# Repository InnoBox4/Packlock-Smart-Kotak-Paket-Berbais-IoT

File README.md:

# Packlock
## Smart-Kotak-Paket-Berbasis-IoT

Proyek ini bertujuan untuk mengembangkan smart kotak paket berbasis IoT bernama PackLock, yang memungkinkan pengguna memantau status keberadaan paket secara real-time melalui dashboard web berbasis PHP. Sistem ini dirancang sebagai solusi pengiriman barang tanpa tatap muka yang aman dan efisien, terutama di era digital saat ini. PackLock dibangun menggunakan Arduino Uno sebagai mikrokontroler utama yang mengatur pembacaan sensor, kontrol aktuator, dan komunikasi data ke server lokal.

Untuk mendeteksi keberadaan paket, sistem menggunakan sensor infrared yang dipasang di dalam kotak. Selain itu, sensor ultrasonik dan reed switch digunakan untuk memantau status pintu depan dan pintu belakang kotak, apakah dalam keadaan tertutup atau terbuka. Ketika kondisi berubah, sistem akan mengirimkan data ke server melalui komunikasi serial dan hasilnya ditampilkan pada web secara real-time. Pengguna juga dapat menerima notifikasi dan melakukan kontrol jarak jauh melalui dashboard, termasuk membuka pintu kotak secara otomatis.

Web dashboard PackLock dibangun menggunakan PHP yang terhubung ke database untuk menyimpan dan menampilkan status terkini dari kotak paket. Dengan antarmuka yang sederhana, pengguna dapat dengan mudah mengetahui apakah terdapat paket di dalam kotak dan apakah pintu dalam keadaan tertutup atau terbuka. Sistem ini diharapkan dapat meningkatkan keamanan dan efisiensi dalam proses pengiriman dan pengambilan paket di lingkungan rumah atau perkantoran cerdas (smart building).

## Support By :
>- Dosen Pengampu : Akhmad Hendriawan ST., MT. (NIP.197501272002121003)
>- Mata kuliah : Workshop Mikrokontroller
>- Program Studi : D3 Teknik Elektronika
>- Politeknik Elektronika Negeri Surabaya<br>

## Team Member :
|      NRP      |            Nama             |         Jobdesk          |
| :-----------: | :-------------------------: | :----------------------: |
| 2123500023    | Muhammad Fariz Ibnu T.H     | Hardware Developer       | 
| 2123500011    | M . Ghozali                 | Mekanik                  | 
| 2123500013    | Gede Satya Prawira Negara   | Programer               | 
| 2123500008    | M . Ragita Dwi Yuliansyah   | Project Manager (PM)                  | 
| 2123500012    | Setyo Budi Utomo            | Mekanik                  | 
| 2123500021    | Adam Surya Waskito          | UI/UX Designer           |

## Komponen Utama 
| Komponen |             Fungsi                | 
|----------|-----------------------------------|                       
|Arduino Uno| pengontrol sistem |
| Ultrasonic Sensor HC-SR04  | deteksi pintu depan tertutup atau tidak |               
|Sensor Infrared (IR) Proximity FC-51 |deteksi paket masuk|
|Reed Switch + Magnet | deteksi pintu belakang terbuka/tertutup)|
|Servo Motor (SG90 / MG90S)|untuk membuka pintu|

## Flyer Packlock

## Cara kerja Packlock

https://github.com/user-attachments/assets/c9181a2b-23b7-4780-8032-19ebb1beb945

## Iklan Produk Packlock

[Video Iklan Produk Packlock](https://youtube.com/shorts/VkG0_1tyrqw?feature=share)

## PPT Packlock

[PPT Packlock](https://www.canva.com/design/DAGpCFjL8s4/J2JU336eNsQ9mIj8pktKxA/edit?utm_content=DAGpCFjL8s4&utm_campaign=designshare&utm_medium=link2&utm_source=sharebutton)

## Desain App di Figma

[Desain App Packlock di Figma](https://www.figma.com/design/fq3XM4EmNfqJVly56ajVYE/Packlock?node-id=0-1&t=N5Q5iODnZTlXCq0t-1)

## Desain 3D di Thingiverse 

[Desain 3D di Thingiverse](https://www.thingiverse.com/setyoo_io/collections/43256436/things)

## Simulasi Program di Wokwi

[Simulasi Program di Wokwi](https://wokwi.com/projects/429229658305672193)

## Video Simulasi Program

[Video Simulasi Program](https://github.com/user-attachments/assets/82a5f85e-70d9-47c1-b36e-2be93320dba2)

## Daftar Isi
- [Komponen Yang Digunakan](#Komponen-Yang-Digunakan)
- [Blok Diagram](#Blok-Diagram)
- [Diagram Arsitektur Sistem](#Diagram-Arsitektur-Sistem)
- [Hardware](#Hardware)
- [Desain UI UX](#Desain-UI-UX)
- [Desain 3D](#Desain-3D)
- [Desain Yang Sudah Jadi](#Desain-Yang-Sudah-Jadi)

## Komponen Yang Digunakan
1.Hardware
- Arduino Uno
- Motor Servo
- Sensor IR Obstacle
- Sensor Ultrasonik
- Conector Molex
- Shield PCB
- Kabel Jumper

2.Software
- Arduino IDE
- Visual Studio Code
- Kicad
- Inventor
- Figma
- Wokwi

3.Alat 
- Palu
- Meteran
- Gergaji
- Penggaris
- bulpoint
- Cutter
- Gunting
- Kuas
- Obeng
- Lem Tembak
- Solder 
  
4.Bahan
- Balok kayu Diameter 2 CM (5 Buah)
- Karton
- Paku Kecil
- Lem kayu
- Cat Kayu
- Paku Pines
- Cat putih
- Timah
- Solasi

## Desain Yang Sudah Jadi

## Blok Diagram

## Diagram Arsitektur Sistem

## [Hardware](https://github.com/InnoBox4/Packlock-Smart-Kotak-Paket-Berbais-IoT/tree/main/HARDWARE)

Berikut ini adalah hasil skematik dari rangkaian Smart Kotak Paket Berbasis IoT menggunakan software KiCad.
<div align="center">

</div>

Berikut ini adalah hasil layout dari rangkaian Smart Kotak Paket Berbasis IoT menggunakan software KiCad.
<div align="center">

</div>

Berikut ini adalah hasil 3D dari rangkaian Smart Kotak Paket Berbasis IoT menggunakan software KiCad.
<div align="center">

</div>

Berikut ini adalah hasil cetak dari rangkaian Smart Kotak Paket Berbasis IoT menggunakan software KiCad.
<div align="center">

</div>

Berikut ini adalah hardware yang sudah terpasang di Packlock.
<div align="center">

</div>

## [Desain UI UX](https://github.com/InnoBox4/Packlock-Smart-Kotak-Paket-Berbais-IoT/tree/main/UI-UX)

Berikut ini adalah UI/UX Web Packlock.
<div align="center">

</div>

## [Desain 3D](https://github.com/InnoBox4/Packlock-Smart-Kotak-Paket-Berbais-IoT/tree/main/DESAIN%203D)

Berikut ini adalah Desain 3D Packlock Bagian Dalam.
<div align="center">

</div>

Berikut ini adalah Desain 3D Packlock Tampak Depan.
<div align="center">

</div>

Berikut ini adalah pembuatan Desain 3D Packlock.

https://github.com/user-attachments/assets/38ecc393-ebad-4563-a7b1-a252cfec6f6e

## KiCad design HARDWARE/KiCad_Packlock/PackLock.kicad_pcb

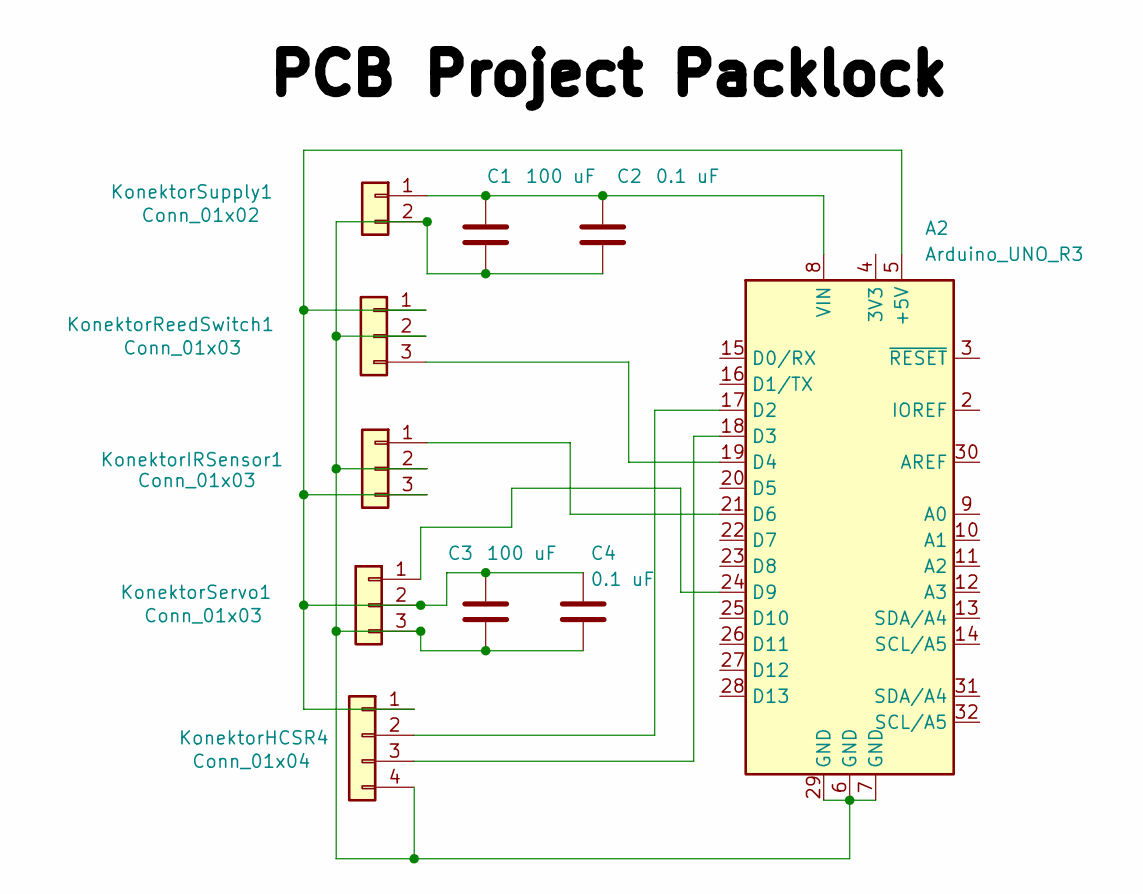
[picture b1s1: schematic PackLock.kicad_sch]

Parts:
A2: Arduino_UNO_R3
C1, C3: 100 uF; C_0805_2012Metric_Pad1.18x1.45mm_HandSolder
C2, C4: 0.1 uF; C_0805_2012Metric_Pad1.18x1.45mm_HandSolder
KonektorHCSR4: Conn_01x04; JST_PH_B4B-PH-K_1x04_P2.00mm_Vertical
KonektorIRSensor1: Conn_01x03; JST_PH_B3B-PH-K_1x03_P2.00mm_Vertical
KonektorReedSwitch1: Conn_01x03; JST_PH_B3B-PH-K_1x03_P2.00mm_Vertical
KonektorServo1: Conn_01x03; JST_PH_B3B-PH-K_1x03_P2.00mm_Vertical
KonektorSupply1: Conn_01x02; JST_PH_B2B-PH-K_1x02_P2.00mm_Vertical

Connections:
unnamed: A2.5 (+5V), C3.1, C4.1, KonektorHCSR4.1, KonektorIRSensor1.3, KonektorReedSwitch1.1, KonektorServo1.2
unnamed: A2.17 (D2), KonektorHCSR4.2
unnamed: A2.18 (D3), KonektorHCSR4.3
unnamed: A2.19 (D4), KonektorReedSwitch1.3
unnamed: A2.21 (D6), KonektorIRSensor1.1
unnamed: A2.24 (D9), KonektorServo1.1
unnamed: A2.8 (VIN), C1.1, C2.1, KonektorSupply1.1
unnamed: A2.6 (GND), A2.7 (GND), A2.29 (GND), C1.2, C2.2, C3.2, C4.2, KonektorHCSR4.4, KonektorIRSensor1.2, KonektorReedSwitch1.2, KonektorServo1.3, KonektorSupply1.2

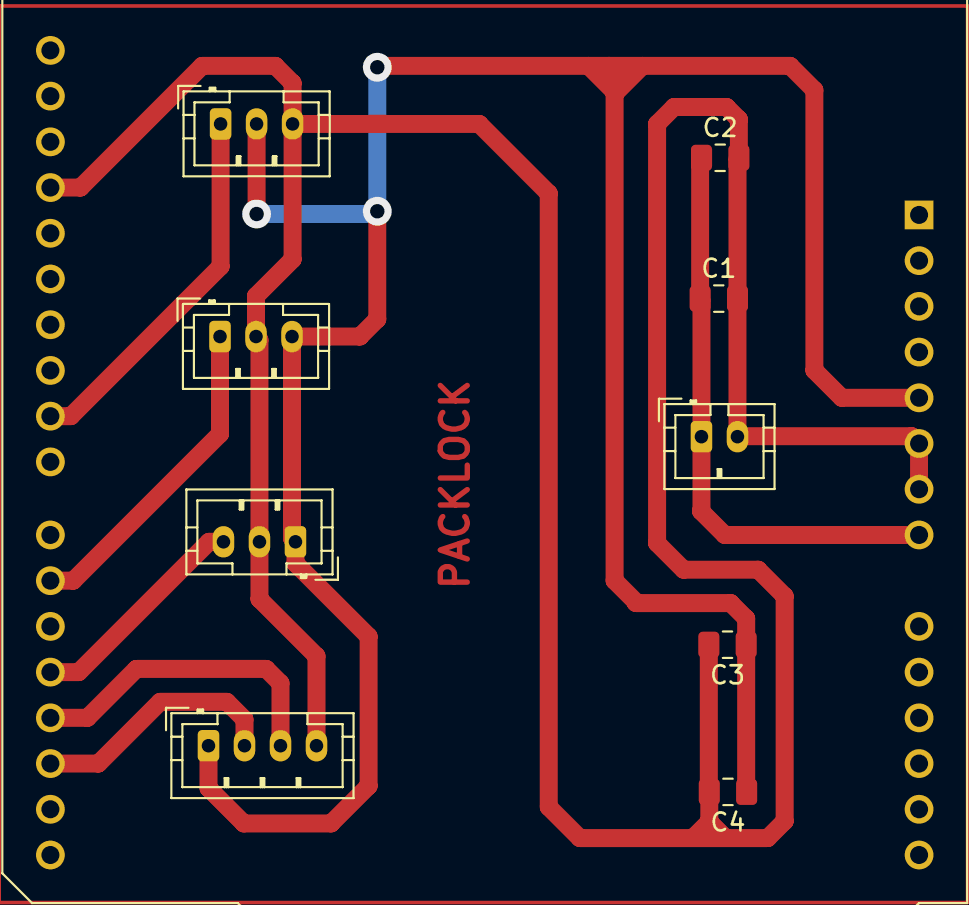
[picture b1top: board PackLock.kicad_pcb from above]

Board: 2 copper layers, 10 parts (0 on the bottom side), 8 nets.

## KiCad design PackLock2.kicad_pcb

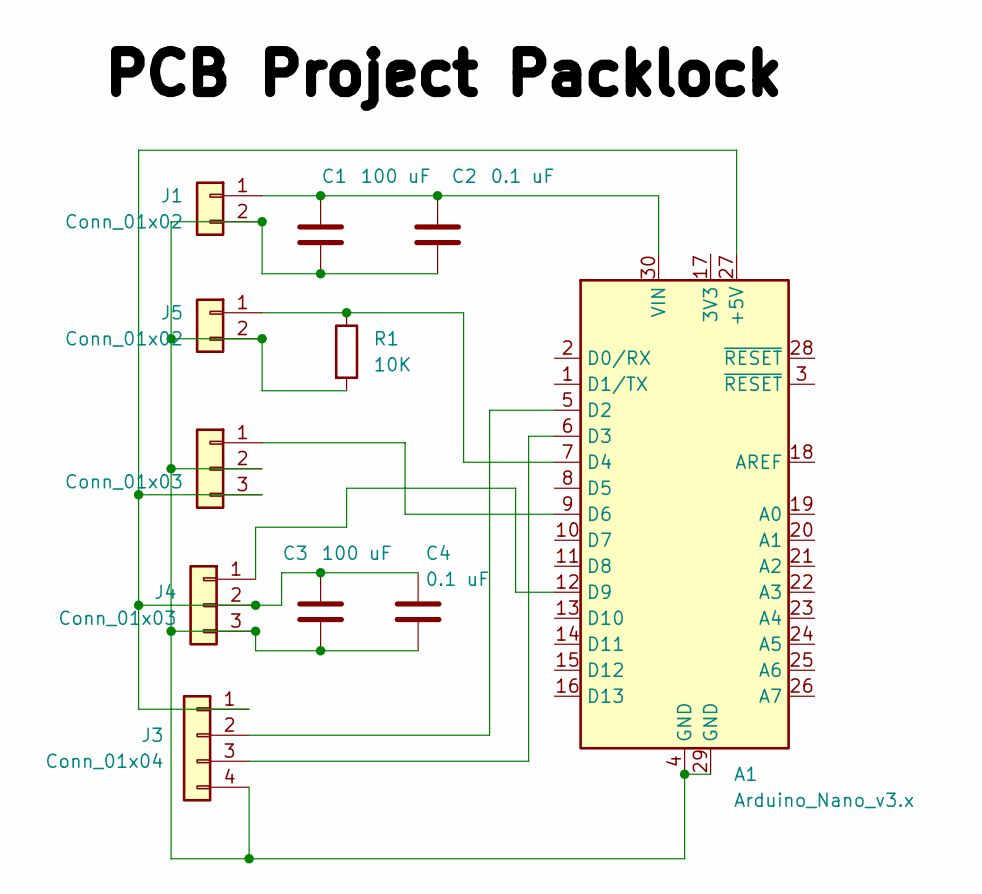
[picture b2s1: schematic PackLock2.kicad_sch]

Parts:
A1: Arduino_Nano_v3.x; Arduino_Nano
C1, C3: 100 uF; CP_Radial_D5.0mm_P2.00mm
C2, C4: 0.1 uF; C_Disc_D3.0mm_W1.6mm_P2.50mm
J1, J5: Conn_01x02; JST_XH_B2B-XH-A_1x02_P2.50mm_Vertical
J2, J4: Conn_01x03; JST_XH_B3B-XH-A_1x03_P2.50mm_Vertical
J3: Conn_01x04; JST_XH_B4B-XH-A_1x04_P2.50mm_Vertical
R1: 10K; R_Axial_DIN0207_L6.3mm_D2.5mm_P7.62mm_Horizontal

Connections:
unnamed 0: A1.27 (+5V), C3.1, C4.1, J2.3, J3.1, J4.2; also elsewhere on the board
unnamed: A1.5 (D2), J3.2
unnamed: A1.6 (D3), J3.3
unnamed: A1.7 (D4), J5.1, R1.1
unnamed 4: A1.9 (D6), J2.1; also elsewhere on the board
unnamed: A1.12 (D9), J4.1
unnamed: A1.30 (VIN), C1.1, C2.1, J1.1
unnamed 7: A1.4 (GND), A1.29 (GND), C1.2, C2.2, C3.2, C4.2, J1.2, J2.2, J3.4, J4.3, J5.2, R1.2; also elsewhere on the board

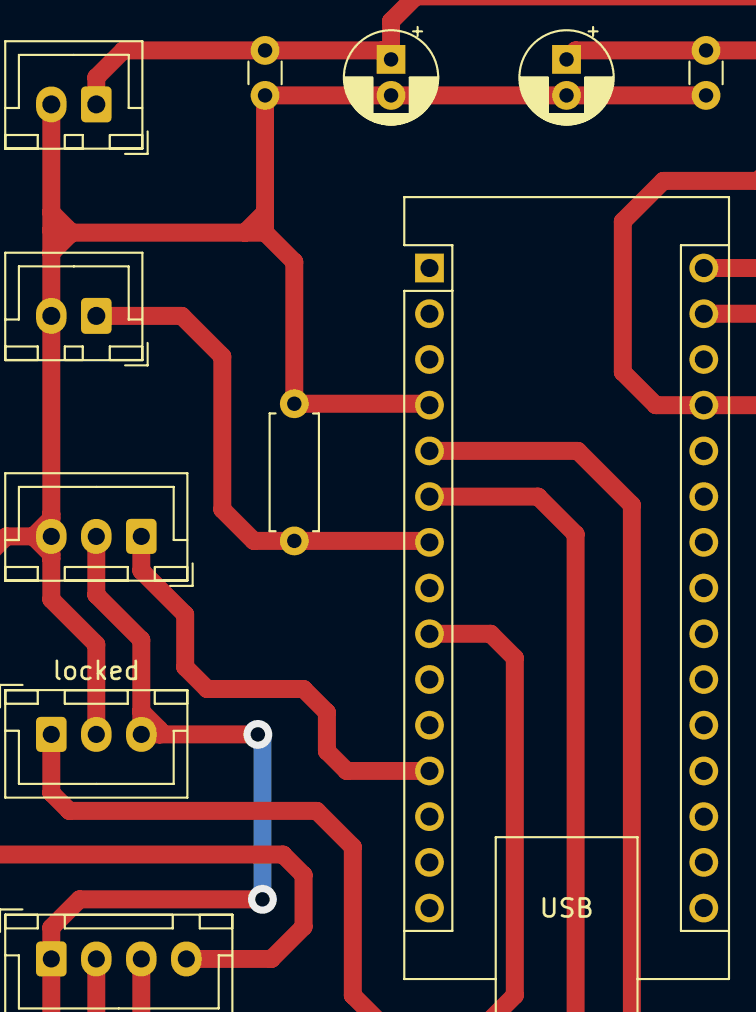
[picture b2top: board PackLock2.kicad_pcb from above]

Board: 2 copper layers, 11 parts (0 on the bottom side), 8 nets.

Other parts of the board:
locked: Conn_01x03; JST_XH_B3B-XH-A_1x03_P2.50mm_Vertical

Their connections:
unnamed 0: locked.3; also elsewhere on the board
unnamed 4: locked.1; also elsewhere on the board
unnamed 7: locked.2; also elsewhere on the board

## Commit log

2025-04-26 Create Desain
2025-04-27 Create Hardware
2025-04-27 Create PCB_Desain
2025-04-27 Rename PCB_Desain to PCB_Desain.png
2025-04-27 Rename PCB_Desain.png to ...
2025-04-27 Rename 3D_PCB_Desain.jpg to Hardware2/3D_PCB_Desain.jpg
2025-04-27 Rename 3D_PCB_Desain.jpg to 3D_PCB_Desain.jpg
2025-04-27 Create DESIGN
2025-04-27 https://drive.google.com/drive/folders/1jaNO3XyE2Z4ibHH0CLo6dLkds-N7lDg7?usp=drive_link
    Berikut merupakan bagian-bagian dari desain 0.1 dan desain 0.2 yang dicantumkan pada gogle drive
    Perbedaan desain sebelum dan setelah revisi :
    Desain 0.1 yaitu lebih sederhana yang mempunyai 2 pintu utama (depan & belakang) kemudian dibagian dalam kosong hanya ada tempat untuk menyimpan komponen hardware tetapi desain ini memiliki banyak ke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
    Desain 0.2 yaitu lebih rumit dan kompleks karena terdapat sekat-sekat yang bertujuan untuk mengamankan paket agar tidak bisa diamb
2025-04-27 Create program
2025-04-27 Rename 3D to 3D
2025-04-27 Create UI Design
2025-04-27 Create UI
2025-04-27 Create UI Design
    https://www.figma.com/design/fq3XM4EmNfqJVly56ajVYE/Packlock?node-id=0-1&t=N5Q5iODnZTlXCq0t-1
2025-04-27 https://www.figma.com/design/fq3XM4EmNfqJVly56ajVYE/Packlock?node-id=0-1&t=N5Q5iODnZTlXCq0t-1
2025-04-27 Create Figma
    https://www.figma.com/design/fq3XM4EmNfqJVly56ajVYE/Packlock?node-id=0-1&t=N5Q5iODnZTlXCq0t-1
2025-04-27 Rename program to Program/Program_Cek_Paket
2025-04-27 Create Program_Kontrol_Pintu
2025-04-28 Rename 3D_PCB_Desain2.jpg to 3D_PCB_Desain2.jpg
2025-04-28 Rename Layout_PCB_Desain.jpg to Layout_PCB_Desain.jpg
2025-04-28 Rename Skematik_PCB_Desain.jpg to Skematik_PCB_Desain.jpg
2025-04-28 Rename Gambar_Simulasi_Kontrol_Pintu.jpg to ar_Simulasi_Kontrol_Pintu.jpg
2025-04-28 Rename Program_Cek_Paket to Program_Cek_Paket
2025-04-28 Rename Program_Kontrol_Pintu to Program_Kontrol_Pintu
2025-05-18 Dokumen
2025-05-18 DOKUMENTASI
2025-05-18 Rename packlock ui uix.jpg to Web Packlock.jpg
2025-05-18 Rename ChatGPT Image May 18, 2025, 10_57_42 PM.png to ASSETS/Poster Packlock.png
2025-05-18 Rename image.png to UI/Web Packlock 2.png
2025-05-18 Rename ChatGPT Image May 19, 2025, 12_11_34 AM.png to Blok Diagram System Architecture.jpg
2025-05-18 Rename ar_Simulasi_Kontrol_Pintu.jpg to Gambar_Simulasi_Kontrol_Pintu.jpg
2025-05-19 Rename Web Packlock 2.png to Web Packlock 2.png
2025-05-19 Rename Web Packlock.jpg to Web Packlock.jpg
2025-05-19 Rename Design 0.1 Tampak Belakang.png to Design 0.1 Tampak Belakang.png
2025-05-19 Rename Design 0.1 Tampak Depan.png to Design 0.1 Tampak Depan.png
2025-05-19 Rename Design 0.2 Bagian Dalam.png to Design 0.2 Bagian Dalam.png
2025-05-19 Rename Design 0.2 Tampak Depan.png to Design 0.2 Tampak Depan.png
2025-05-31 Rename 3D_PCB_Desain_Final.jpg.png to 3D_PCB_Desain_Final.jpg
2025-05-31 Rename 3D_PCB_Desain_Final2.jpg.png to 3D_PCB_Desain_Final2.jpg
2025-05-31 Rename Layout_PCB_Desain_Final.jpg.png to Layout_PCB_Desain_Final.jpg
2025-05-31 Rename Skematik_PCB_Desain_Final.jpg.png to Skematik_PCB_Desain_Final.jpg
2025-05-31 Rename 3D_PCB_Desain3.jpg to 3D_PCB_Desain3.jpg
2025-05-31 Rename Layout_PCB_Desain2.jpg to Layout_PCB_Desain2.jpg
2025-05-31 Rename PCB_Jadi.jpg to PCB_Jadi.jpg
2025-05-31 Rename PCB_Jadi2.jpg to PCB_Jadi2.jpg
2025-05-31 Rename PCB_Jadi_Final.jpg to PCB_Jadi_Final.jpg
2025-05-31 Rename PCB_Jadi_Final2.jpg to PCB_Jadi_Final2.jpg
2025-05-31 Rename Skematik_PCB_Desain2.jpg to Skematik_PCB_Desain2.jpg
2025-05-31 Rename Web Packlock 2.png to Web Packlock.png
2025-05-31 Rename UI-UX_WEB_PACKLOCK.png to Web Packlock Final.png
2025-05-31 Rename Poster Packlock.png to Logo Packlock.png
2025-05-31 Rename Tambahkan subjudul.png to Diagram Arsitektur Sistem.png
2025-06-01 Rename Untitled Diagram.drawio.png to Blok Diagram.png
2025-06-01 Update README.md - Add Video and image files
2025-06-01 Update README.md - Add Video,gif and image files
2025-06-02 Create program pack lock
2025-06-02 Rename Tambahkan judul.png to Flyer Packlock.jpg
2025-06-02 Rename program pack lock to Program Packlock
2025-06-02 Rename PackLock-Smart-Locker-Otomatis-Berbasis-IoT.pptx.pptx to PackLock-Smart-Locker-Otomatis-Berbasis-IoT.pptx.pptx
2025-06-06 Rename 2025-06-06 16-01-08.mkv to ASSETS/2025-06-06 16-01-08.mkv
2025-06-06 Rename 2025-06-06 16-01-08.mp4 to hapus/2025-06-06 16-01-08.mp4
2025-06-06 Create Program Simulasi Packlock
